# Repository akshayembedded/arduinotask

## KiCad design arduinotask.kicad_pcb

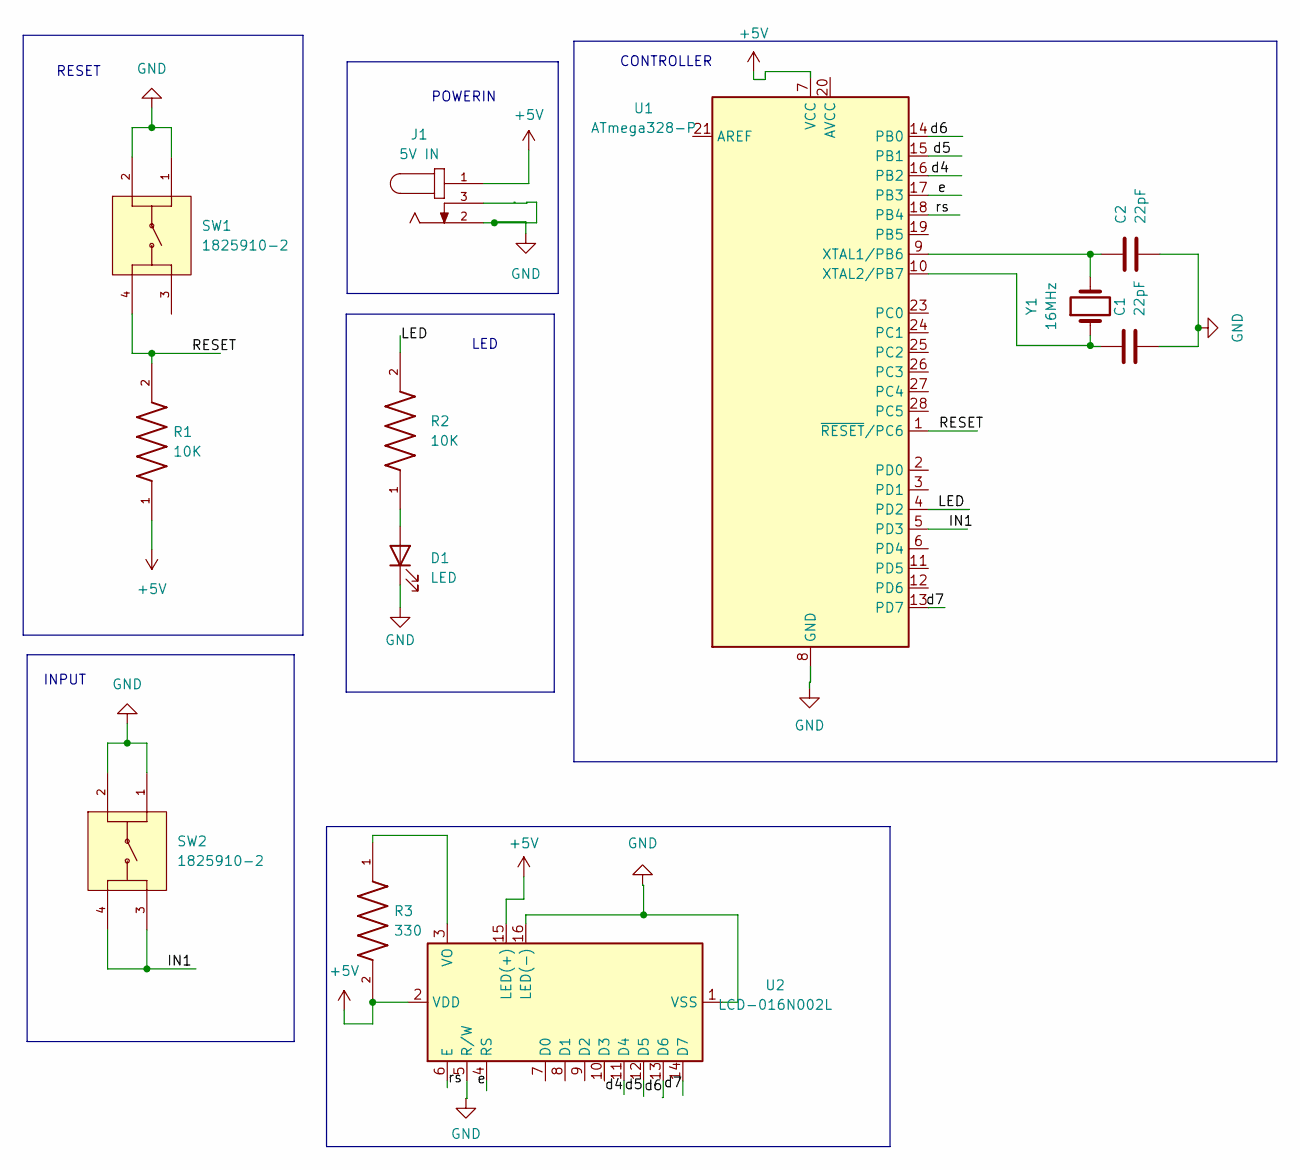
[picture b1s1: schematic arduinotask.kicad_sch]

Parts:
C1, C2: 22pF; C_Disc_D3.0mm_W1.6mm_P2.50mm
D1: LED; LED_D3.0mm
J1: 5V IN; CUI_PJ-002B
R1, R2: 10K; RESAD700W45L350D185; Voltage_Rating 200 V; Tolerance 5%
R3: 330; RESAD700W45L350D185; Voltage_Rating 200 V; Tolerance 5%
SW1, SW2: 1825910-2; TE_1825910-2
U1: ATmega328-P; DIP-28_W7.62mm
U2: LCD-016N002L; PinHeader_1x16_P2.54mm_Vertical
Y1: 16MHz; Crystal_HC18-U_Vertical

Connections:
+5V: J1.1, R1.1, R3.2, U1.7 (VCC), U2.2 (VDD), U2.15 (LED(+))
/IN1: SW2.3, SW2.4, U1.5 (PD3)
/LED: R2.2, U1.4 (PD2)
/RESET: R1.2, SW1.4, U1.1 (~RESET/PC6)
/d4: U1.16 (PB2), U2.11 (D4)
/d5: U1.15 (PB1), U2.12 (D5)
/d6: U1.14 (PB0), U2.13 (D6)
/d7: U1.13 (PD7), U2.14 (D7)
/e: U1.17 (PB3), U2.4 (RS)
/rs: U1.18 (PB4), U2.6 (E)
GND: C1.2, C2.2, D1.1 (K), J1.2, J1.3, SW1.1, SW1.2, SW2.1, SW2.2, U1.8 (GND), U1.22 (GND), U2.1 (VSS), U2.5 (R/W), U2.16 (LED(-))
unnamed: D1.2 (A), R2.1
unnamed: C2.1, U1.9 (XTAL1/PB6), Y1.2
unnamed: C1.1, U1.10 (XTAL2/PB7), Y1.1
unnamed: R3.1, U2.3 (VO)

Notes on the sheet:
CONTROLLER
LED
INPUT
POWERIN
RESET

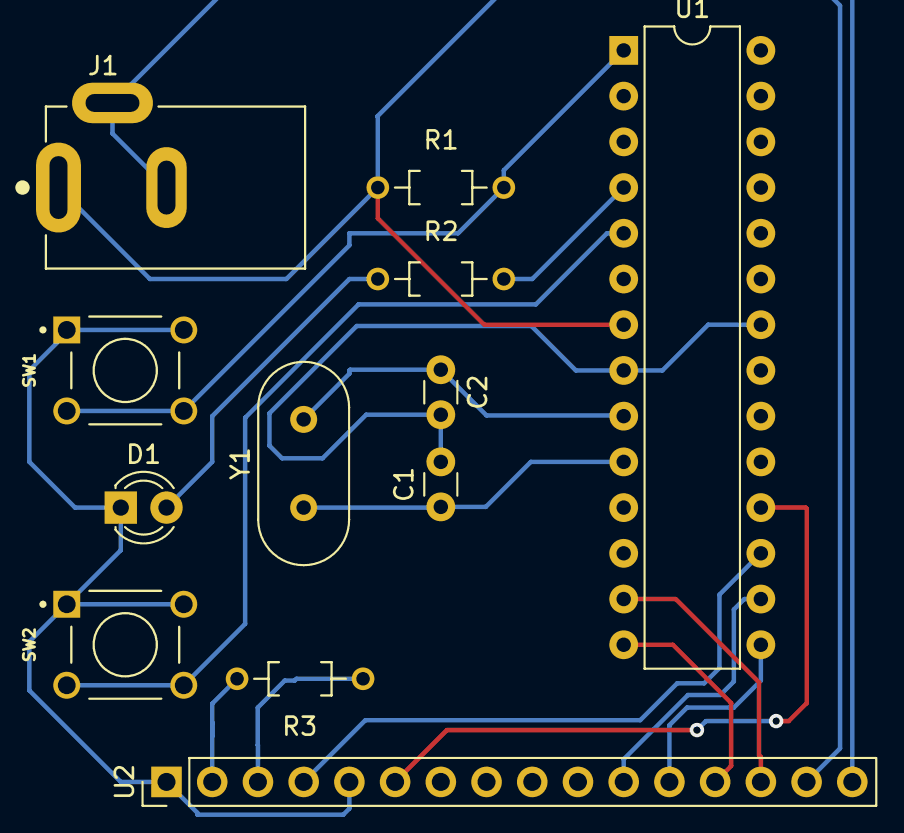
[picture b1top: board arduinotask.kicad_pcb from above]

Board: 2 copper layers, 12 parts (0 on the bottom side), 15 nets.

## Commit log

2023-08-08 second commit
